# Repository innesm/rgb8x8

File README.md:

# rgb8x8
board for common-anode 8x8 RGB led panel driven with shift registers

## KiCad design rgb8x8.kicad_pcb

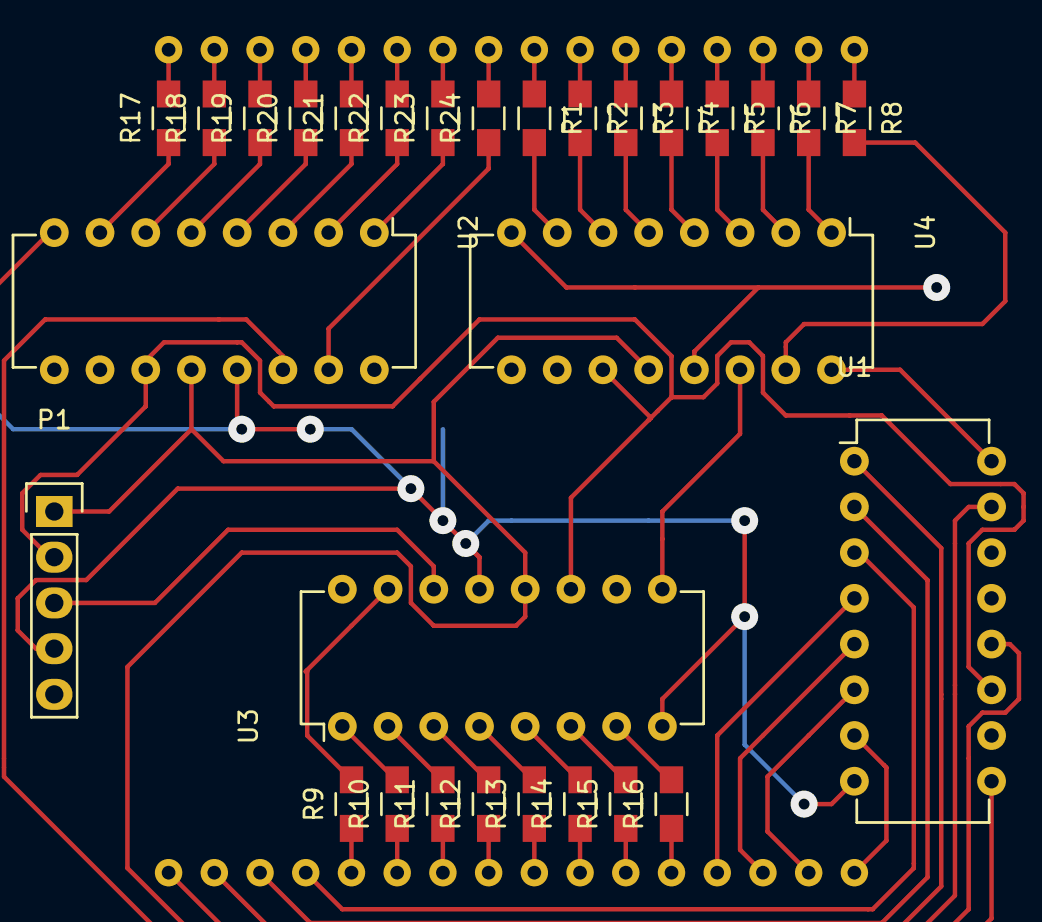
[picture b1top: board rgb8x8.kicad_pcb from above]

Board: 2 copper layers, 30 parts (0 on the bottom side), 64 nets.

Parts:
P1: CONN_01X05; Pin_Header_Straight_1x05
R1, R2, R3, R4, R5, R6, R7, R8: 120; R_0805_HandSoldering
R9, R10, R11, R12, R13, R14, R15, R16, R17, R18, R19, R20, R21, R22, R23, R24: 82; R_0805_HandSoldering
RGB1: GTM2088; GTM2088-LED
U1, U2, U3, U4: 74HC595; DIP-16_W7.62mm

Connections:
+5V: P1.5, U1.10, U1.16, U2.10, U2.16, U3.10, U3.16, U4.10, U4.16
/B1: R17.1, U2.7
/B2: R18.1, U2.6
/B3: R19.1, U2.5
/B4: R20.1, U2.4
/B5: R21.1, U2.3
/B6: R22.1, U2.2
/B7: R23.1, U2.1
/B8: R24.1, U2.15
/G1: R9.2, U3.15
/G2: R10.2, U3.1
/G3: R11.2, U3.2
/G4: R12.2, U3.3
/G5: R13.2, U3.4
/G6: R14.2, U3.5
/G7: R15.2, U3.6
/G8: R16.2, U3.7
/R1: R1.2, U4.7
/R2: R2.2, U4.6
/R3: R3.2, U4.5
/R4: R4.2, U4.4
/R5: R5.2, U4.3
/R6: R6.2, U4.2
/R7: R7.2, U4.1
/R8: R8.2, U4.15
/RCLK: P1.1, U1.12, U2.12, U3.12, U4.12
/ROW1: RGB1.17, U1.7
/ROW2: RGB1.18, U1.6
/ROW3: RGB1.19, U1.5
/ROW4: RGB1.20, U1.4
/ROW5: RGB1.29, U1.3
/ROW6: RGB1.30, U1.2
/ROW7: RGB1.31, U1.1
/ROW8: RGB1.32, U1.15
/SER: P1.3, U3.14
/SER12: U1.9, U2.14
/SER34: U3.9, U4.14
/SER41: U1.14, U4.9
/SRCLK: P1.2, U1.11, U2.11, U3.11, U4.11
GND: P1.4, U1.8, U1.13, U2.8, U2.13, U3.8, U3.13, U4.8, U4.13
unnamed: R1.1, RGB1.9
unnamed: R2.1, RGB1.10
unnamed: R3.1, RGB1.11
unnamed: R4.1, RGB1.12
unnamed: R5.1, RGB1.13
unnamed: R6.1, RGB1.14
unnamed: R7.1, RGB1.15
unnamed: R8.1, RGB1.16
unnamed: R9.1, RGB1.28
unnamed: R10.1, RGB1.27
unnamed: R11.1, RGB1.26
unnamed: R12.1, RGB1.25
unnamed: R13.1, RGB1.24
unnamed: R14.1, RGB1.23
unnamed: R15.1, RGB1.22
unnamed: R16.1, RGB1.21
unnamed: R17.2, RGB1.1
unnamed: R18.2, RGB1.2
unnamed: R19.2, RGB1.3
unnamed: R20.2, RGB1.4
unnamed: R21.2, RGB1.5
unnamed: R22.2, RGB1.6
unnamed: R23.2, RGB1.7
unnamed: R24.2, RGB1.8
